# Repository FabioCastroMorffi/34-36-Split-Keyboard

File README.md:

# Raw Split
## Overview

Raw Split is a wired 36 key split keyboard made with 3 PCB layers and powered by an RP pico 2040 on each side. I'm using the Miryoku ZMK as the layout and  I decided to go for a smaller split keyboard for two main reasons: I want it to be portable, mainly so I can use it in class, and I wanted to be under (or very close to) the 50$ mark.

## Motivation
After finishing my design for Hackpad, which was an introduction to PCB Design and 3D modelling, I was confident I could go build a bigger project in a more efficient manner but I was completely wrong. I got sent to the Valley of Stupidity earlier than expected. 

I had an initial idea with a Split Keyboard that would have magnetic sides but I wasn't proud of the design I came up with (and it wasnt printable) so I decided to scrap it up and do it again with a different idea. The change was mainly on the fact that I abhorred 3D modelling of the top/side and bottom so on the Raw Split I decided to only use PCBs for the full design; the raw aesthetic of the build is where the name comes from -- I'm not very creative with names.

## PCBs

### Center

### Top

### Bottom

## CAD
[Direct link on Onshape](https://cad.onshape.com/documents/60adbd5316aad71d4d3bcb16/w/73c77201f5fbc04cf68d7350/e/32bb371216fb4a7634cbbee2?renderMode=0&uiState=686715ac173d9866c8e98733)

Thank you Onshape for being so easy to work with (shame on the horrible experience that is Fusion360's online services for students). I really need to emphasize how much better OnShape is on web, because the initial horrible experience I had with Fusion Online or trying to install a Linux version of Fusion was horrible and made me waste a lot of time. 

Here's the overview of the right split:

The total height of the keyboard will be 24.8 mm. The three PCBs measure 1.6 mm in height, the small standoff will have a height of 4 mm while the big one will have a size 6 mm. Finally the height from the top plate to the top of the keycap is approximally 10 mm. 

## BOM

| Quantity | Item                                 | Price (CAD) | Vendor         | Link                                                                 |
|----------|--------------------------------------|-------------|----------------|----------------------------------------------------------------------|
| 2        | RP Pico 2040 Green with Pin          | 6.42        | Aliexpress     | [Link](https://shorturl.at/I2swX)       |
| 1        | 40 PCS kailh box V2 (linear switches)| 1.38(with welcome deal)      | Aliexpress     | [Link](https://www.aliexpress.com/item/1005005704076690.html) |                                                  
| 1        | 100 PCS Through Hole Diodes (1N4148) | 2.80        | Aliexpress     | [Link](https://shorturl.at/UQSGh)     |
| 2        | 0.91 Inch 128x32 Oled Display        | 5.00        | Aliexpress     | [Link](https://www.aliexpress.com/item/32709141534.html)            |
| 2        | 20 pcs Blank DSA Keycaps             | 12.5        | Aliexpress     | [link](https://shorturl.at/4GHxS)                                   |
| 1        | 10 PCS PJ-320A Jack Receptacle       | 1.58        | Aliexpress     | [Link](https://www.aliexpress.com/item/1005004960903273.html)       |
| 1        | 20 pcs SW-Push 6x6x4.3mm             | 0.26        | Aliexpress     | [Link](https://shorturl.at/fNnse) |
| 1        | 50 pcs Brass Female to Female Standoffs M2x3mm | 2.72        | Aliexpress     | [Link](https://shorturl.at/DMM1S)|
| 1        | 50 pcs Nylon Female to Female Standoffs M2x6mm | 1.28        | Aliexpress     | [Link](https://shorturl.at/DEXHc)
| 2        | 50 pcs M2 5mm and M2 10 mm           | 4.5         | Aliexpress | [Link](https://shorturl.at/Y6ADS) |
| 1        | Antislip Circular Pads 2mm           | 2.97        | Aliexpress | [Link](https://shorturl.at/uavc9)
| 1        | PCB Manufacturing Center             | 13.04  (without coupon)     | JLCPCB         | 
| 1        | PCB Manufacturing Top                | 12.64  (without coupon)     | JLCPCB         |
| 1        | PCB Manufacturing Bottom             | 12.50  (without coupon)     | JLCPCB         |

|Total (CAD, after taxes and after 20$ JLcPCB Coupon)| Total (USD, after taxes and after 20$ JLcPCB Coupon)|
|---------------|--|
|69|50.69|

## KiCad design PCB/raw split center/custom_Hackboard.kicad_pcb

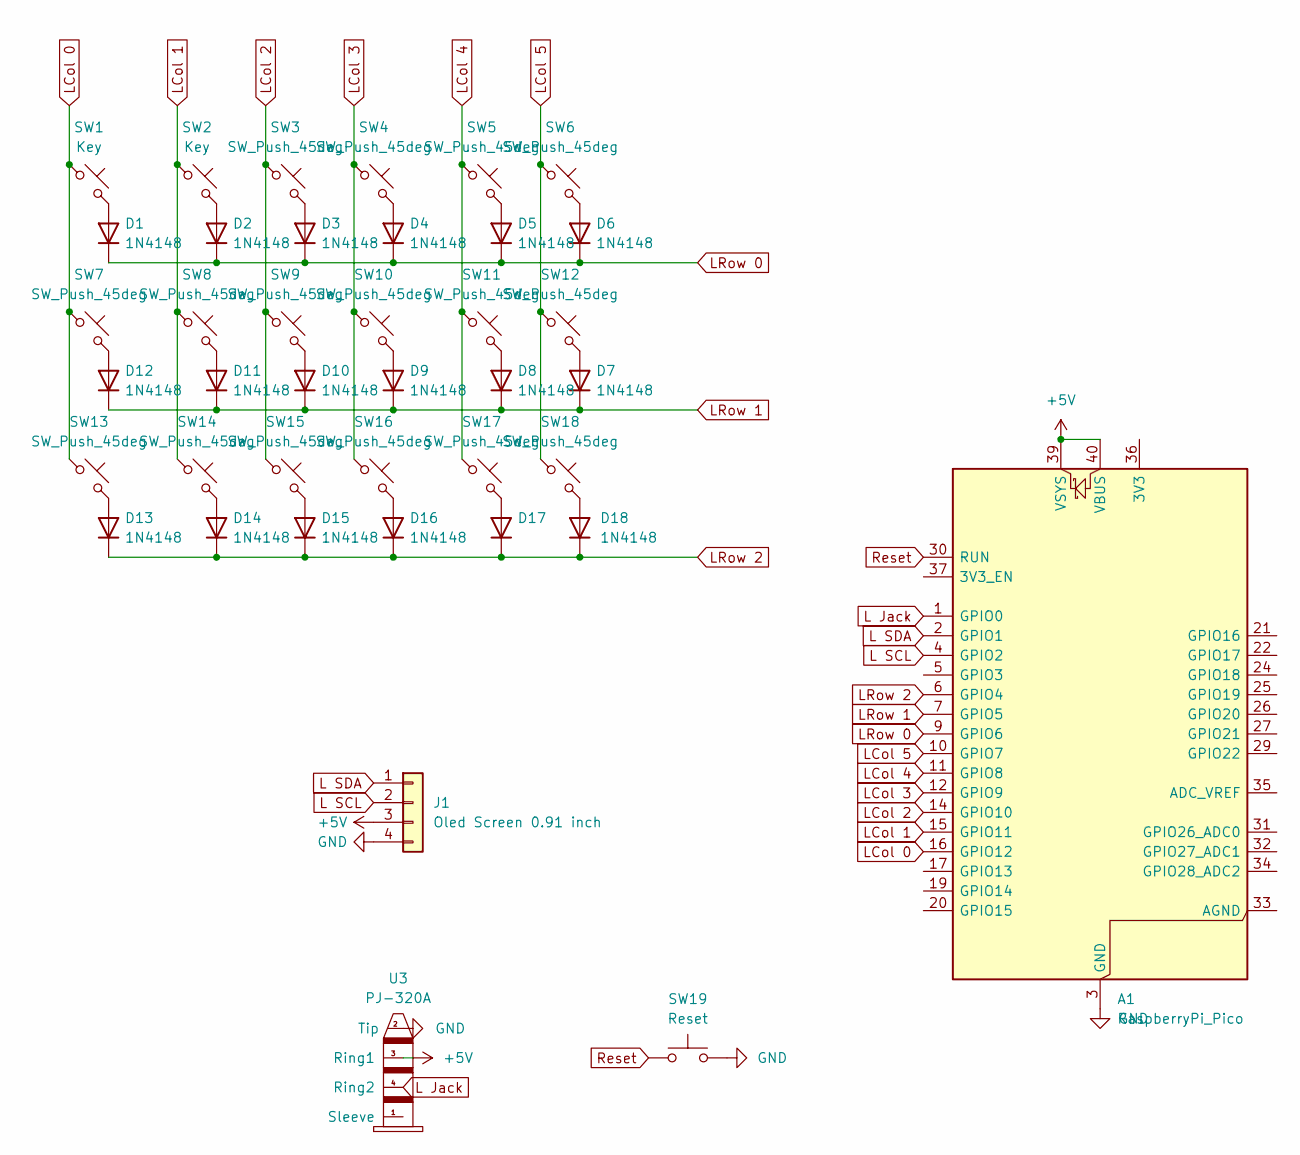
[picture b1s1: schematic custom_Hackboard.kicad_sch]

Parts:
A1: RaspberryPi_Pico; RaspberryPi_Pico_Common_Unspecified
D1, D2, D3, D4, D5, D6, D7, D8, D9, D10, D11, D12, D13, D14, D15, D16, D17, D18: 1N4148; D_DO-35_SOD27_P7.62mm_Horizontal
J1: Oled Screen 0.91 inch; SSD1306-0.91-OLED-4pin-128x32
SW1, SW2: Key; Cherry MX 1u
SW3, SW4, SW5, SW6, SW7, SW8, SW9, SW10, SW11, SW12, SW13, SW14, SW15, SW16, SW17, SW18: SW_Push_45deg; Cherry MX 1u
SW19: Reset; SW_PUSH_6mm_H5mm
U3: PJ-320A

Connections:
+5V: A1.39 (VSYS), A1.40 (VBUS), J1.3, U3.3 (Ring1)
GND: A1.3 (GND), A1.8 (GND), A1.13 (GND), A1.18 (GND), A1.23 (GND), A1.28 (GND), A1.38 (GND), J1.4, SW19.2, U3.2 (Tip); also elsewhere on the board
L Jack: A1.1 (GPIO0), U3.4 (Ring2)
L SCL: A1.4 (GPIO2), J1.2
L SDA: A1.2 (GPIO1), J1.1
LCol 0: A1.16 (GPIO12), SW1.1, SW7.1, SW13.1
LCol 1: A1.15 (GPIO11), SW2.1, SW8.1, SW14.1
LCol 2: A1.14 (GPIO10), SW3.1, SW9.1, SW15.1
LCol 3: A1.12 (GPIO9), SW4.1, SW10.1, SW16.1
LCol 4: A1.11 (GPIO8), SW5.1, SW11.1, SW17.1
LCol 5: A1.10 (GPIO7), SW6.1, SW12.1, SW18.1
LRow 0: A1.9 (GPIO6), D1.1 (K), D2.1 (K), D3.1 (K), D4.1 (K), D5.1 (K), D6.1 (K)
LRow 1: A1.7 (GPIO5), D7.1 (K), D8.1 (K), D9.1 (K), D10.1 (K), D11.1 (K), D12.1 (K)
LRow 2: A1.6 (GPIO4), D13.1 (K), D14.1 (K), D15.1 (K), D16.1 (K), D17.1 (K), D18.1 (K)
unnamed: D1.2 (A), SW1.2
unnamed: D2.2 (A), SW2.2
unnamed: D3.2 (A), SW3.2
unnamed: D4.2 (A), SW4.2
unnamed: D5.2 (A), SW5.2
unnamed: D6.2 (A), SW6.2
unnamed: D7.2 (A), SW12.2
unnamed: D8.2 (A), SW11.2
unnamed: D9.2 (A), SW10.2
unnamed: D10.2 (A), SW9.2
unnamed: D11.2 (A), SW8.2
unnamed: D12.2 (A), SW7.2
unnamed: D13.2 (A), SW13.2
unnamed: D14.2 (A), SW14.2
unnamed: D15.2 (A), SW15.2
unnamed: D16.2 (A), SW16.2
unnamed: D17.2 (A), SW17.2
unnamed: D18.2 (A), SW18.2
Reset: A1.30 (RUN), SW19.1; also elsewhere on the board

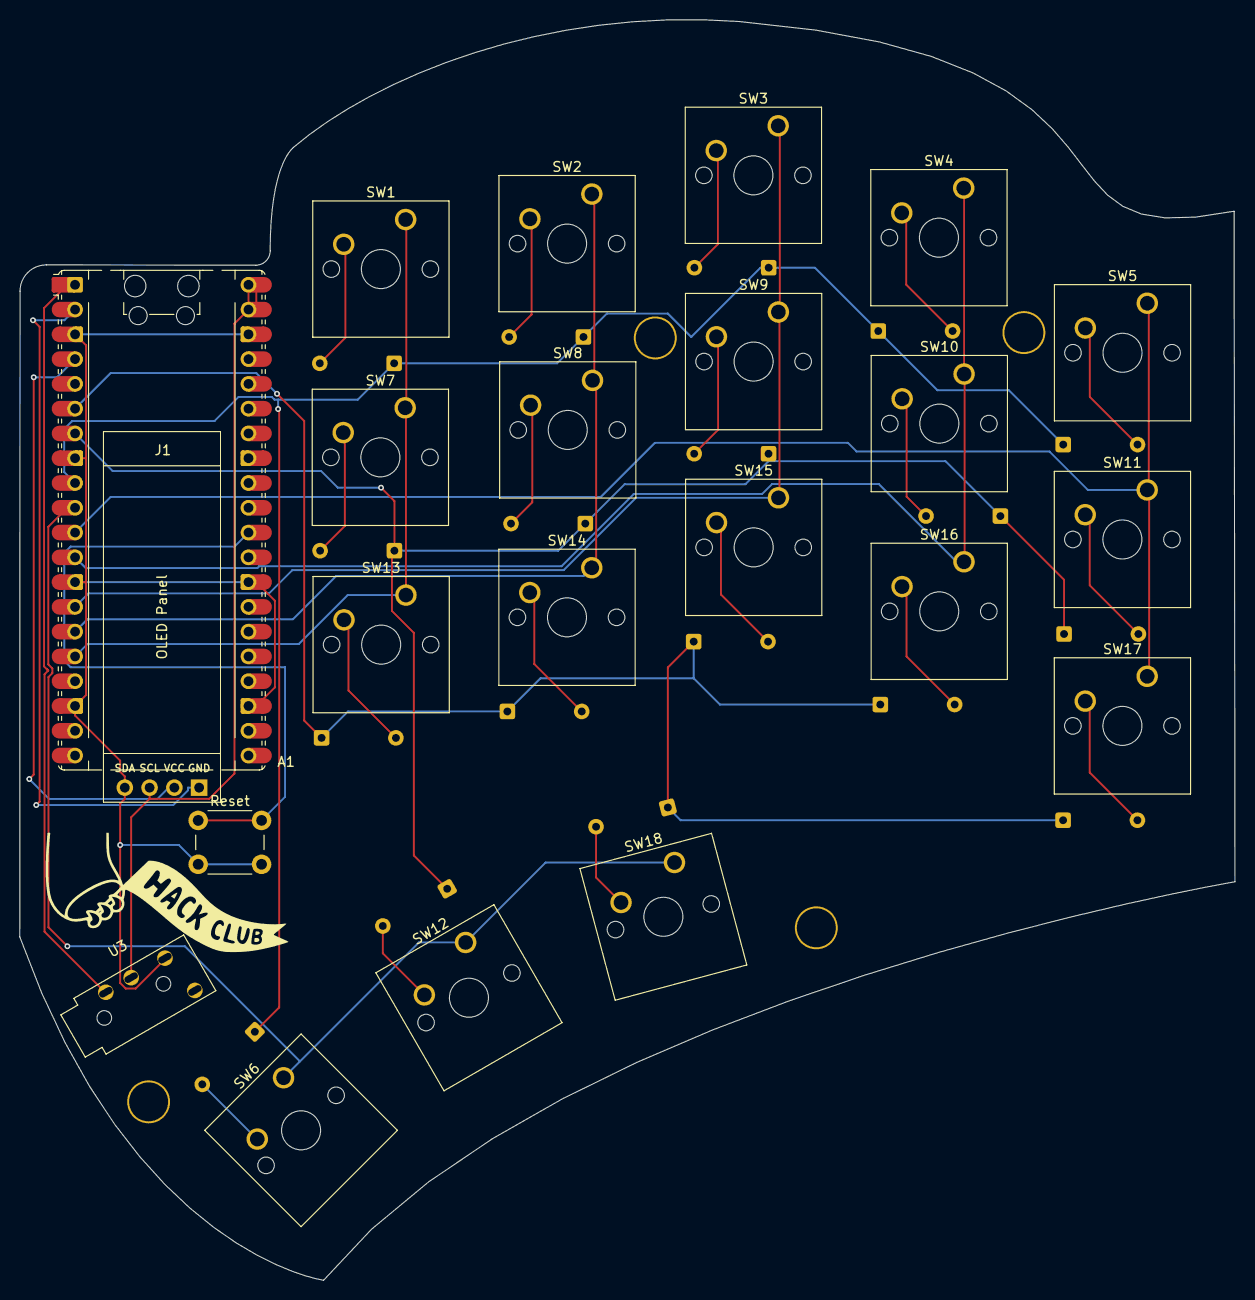
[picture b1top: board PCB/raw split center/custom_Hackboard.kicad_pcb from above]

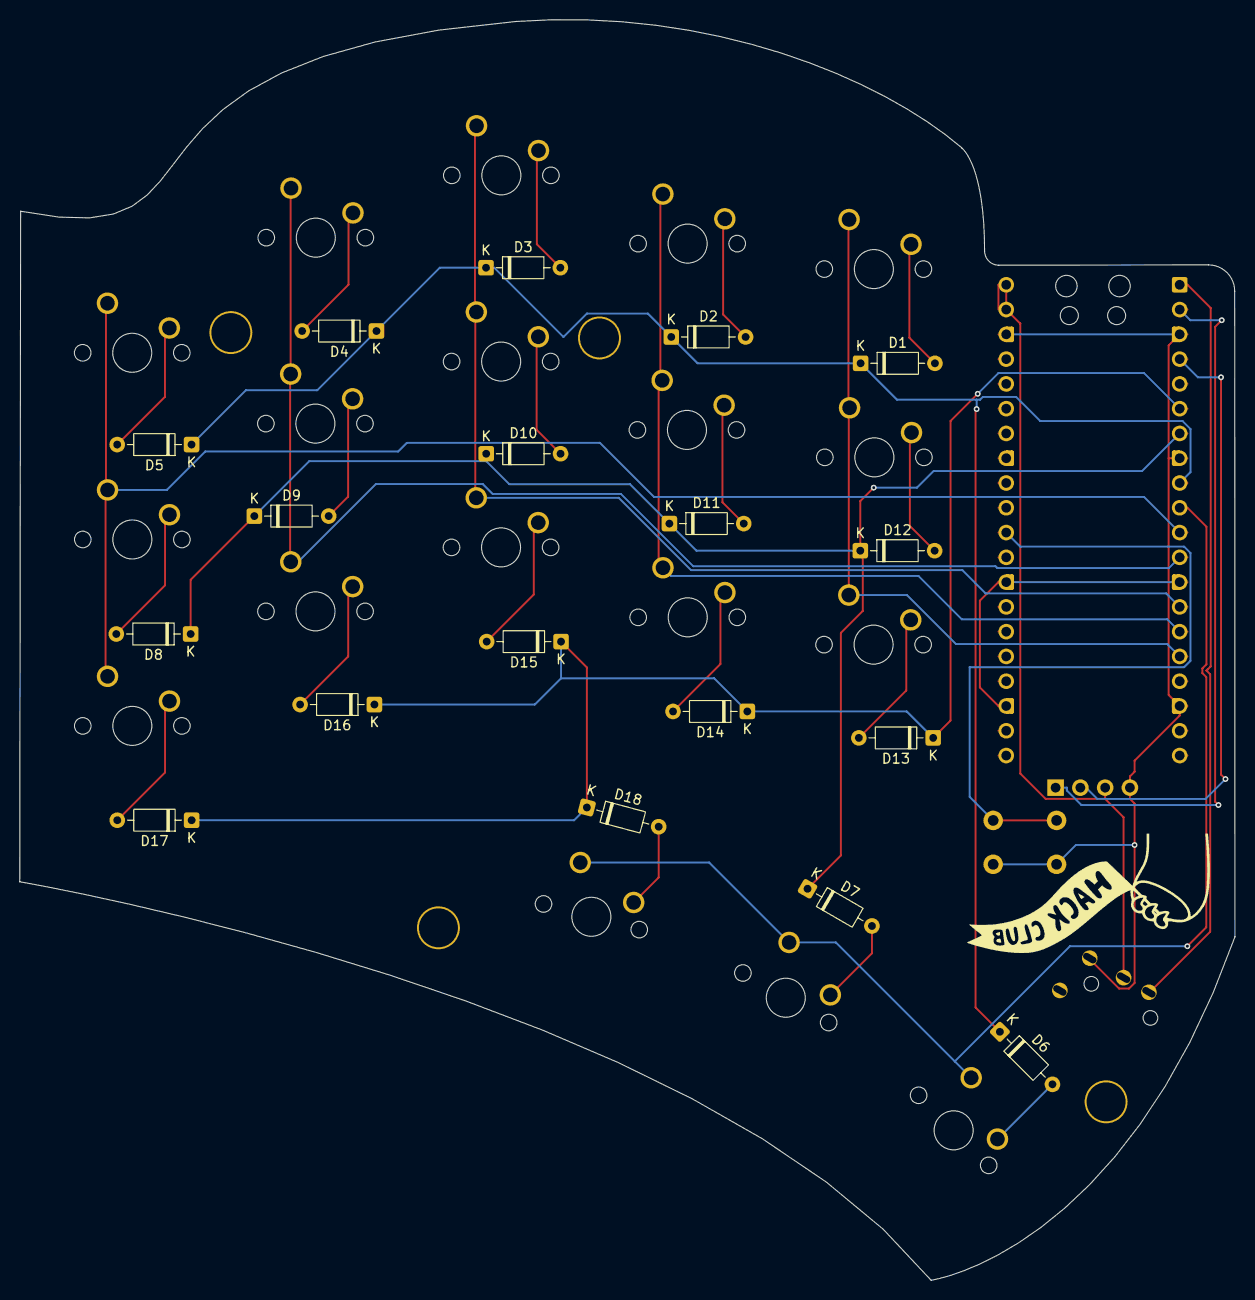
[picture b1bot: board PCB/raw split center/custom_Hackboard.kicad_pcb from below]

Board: 2 copper layers, 124.6 x 129.2 mm, 42 parts (19 on the bottom side), 33 nets.

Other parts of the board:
  : LOGO; hackclub
  #2: LOGO; hackclub
Reset: Reset; SW_PUSH_6mm_H5mm

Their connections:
GND: Reset.2; also elsewhere on the board
Reset: Reset.1; also elsewhere on the board

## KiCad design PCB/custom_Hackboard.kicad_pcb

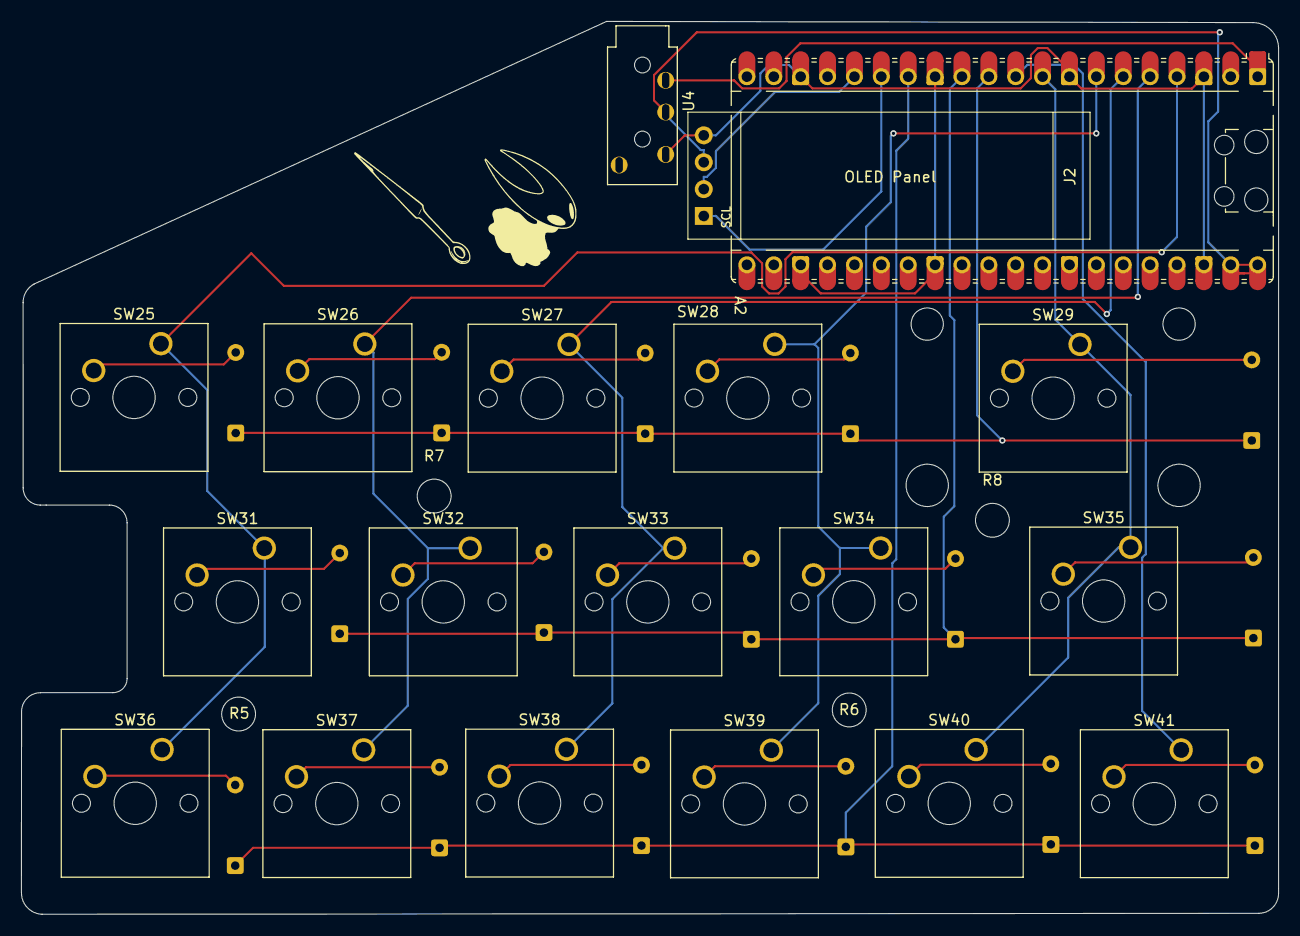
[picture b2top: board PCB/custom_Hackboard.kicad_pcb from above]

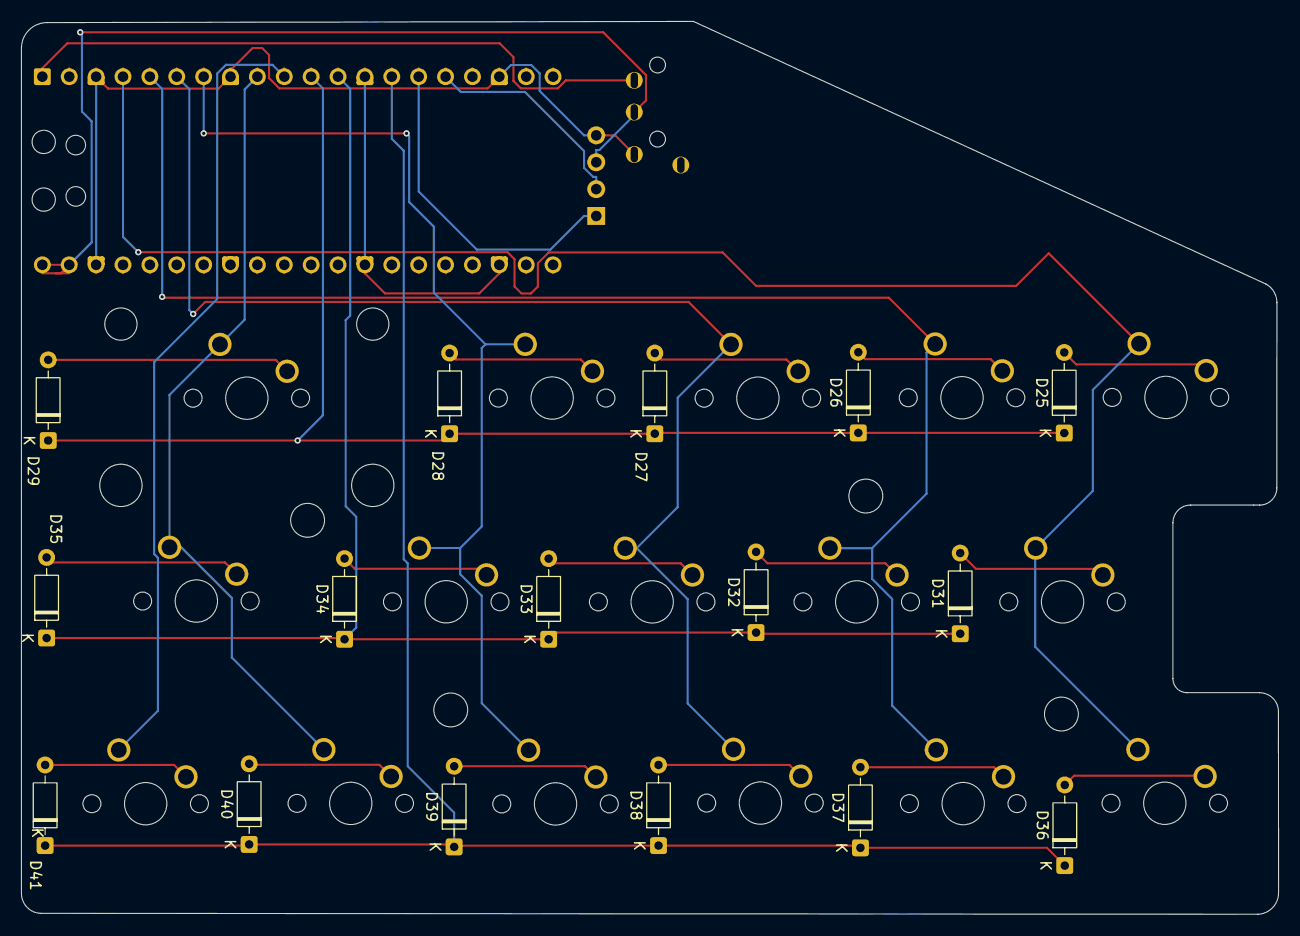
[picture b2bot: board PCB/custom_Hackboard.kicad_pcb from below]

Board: 2 copper layers, 118.8 x 84.4 mm, 40 parts (16 on the bottom side), 30 nets.

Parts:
  : LOGO; hornet_needle
A2: RaspberryPi_Pico; RaspberryPi_Pico_Common_Unspecified
D25, D26, D27, D28, D29, D31, D32, D33, D34, D35, D36, D37, D38, D39, D40, D41: 1N4148; D_DO-35_SOD27_P7.62mm_Horizontal
J2: Conn_01x04; SSD1306-0.91-OLED-4pin-128x32
R5, R6, R7, R8: MountingHole_3.2mm_M3_ISO7380
SW25, SW26, SW27, SW28, SW31, SW32, SW33, SW34, SW36, SW37, SW38, SW39, SW40, SW41: SW_Push_45deg; Cherry MX 1u
SW29: SW_Push_45deg; SW_Cherry_MX_2.00u_PCB
SW35: SW_Push_45deg; SW_Cherry_MX_1.50u_PCB
U4: PJ-320A

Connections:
/GND_R: A2.3 (GND), A2.8 (GND), A2.13 (GND), A2.18 (GND), A2.23 (GND), A2.28 (GND), A2.38 (GND), J2.4, U4.2 (Tip)
/PWR_R: A2.39 (VSYS), A2.40 (VBUS), J2.3, U4.3 (Ring1)
unnamed: D25.2 (A), SW25.2
unnamed: D26.2 (A), SW26.2
unnamed: D27.2 (A), SW27.2
unnamed: D28.2 (A), SW28.2
unnamed: D29.2 (A), SW29.2
unnamed: D31.2 (A), SW31.2
unnamed: D32.2 (A), SW32.2
unnamed: D33.2 (A), SW33.2
unnamed: D34.2 (A), SW34.2
unnamed: D35.2 (A), SW35.2
unnamed: D36.2 (A), SW36.2
unnamed: D37.2 (A), SW37.2
unnamed: D38.2 (A), SW38.2
unnamed: D39.2 (A), SW39.2
unnamed: D40.2 (A), SW40.2
unnamed: D41.2 (A), SW41.2
R Jack: A2.1 (GPIO0), U4.4 (Ring2)
R SCL: A2.16 (GPIO12), J2.2
R SDA: A2.15 (GPIO11), J2.1
RCol 0: A2.4 (GPIO2), SW25.1, SW31.1, SW36.1
RCol 1: A2.5 (GPIO3), SW26.1, SW32.1, SW37.1
RCol 2: A2.6 (GPIO4), SW27.1, SW33.1, SW38.1
RCol 3: A2.7 (GPIO5), SW28.1, SW34.1, SW39.1
RCol 4: A2.9 (GPIO6), SW29.1, SW35.1, SW40.1
RCol 5: A2.10 (GPIO7), SW41.1
RRow 0: A2.11 (GPIO8), D25.1 (K), D26.1 (K), D27.1 (K), D28.1 (K), D29.1 (K)
RRow 1: A2.12 (GPIO9), D31.1 (K), D32.1 (K), D33.1 (K), D34.1 (K), D35.1 (K)
RRow 2: A2.14 (GPIO10), D36.1 (K), D37.1 (K), D38.1 (K), D39.1 (K), D40.1 (K), D41.1 (K)

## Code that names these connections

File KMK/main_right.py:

import board
import displayio
import terminalio
import busio

from kb import KMKKeyboard
from kmk.scanners import DiodeOrientation
from kmk.keys import KC
from kmk.modules.layers import Layers
from kmk.modules.split import Split, SplitSide, SplitType

from adafruit_display_text import label
from adafruit_ssd1306 import SSD1306_I2C

keyboard = KMKKeyboard()

# Pins
keyboard.col_pins = (board.GPIO12, board.board.GPIO11, board.GPIO10, board.GPIO9, board.GPIO8, board.GPIO7)
keyboard.row_pins = (board.GPIO6, board.GPIO5, board.GPIO4)
keyboard.diode_orientation = DiodeOrientation.COL2ROW

#Oled for text display

displayio.release_displays()
i2c = busio.I2C(board.GPIO1, board.GPIO2)  # might reverse SDA and SCL if incorrect

display = SSD1306_I2C(38, 12, i2c)
splash = displayio.Group()

text_area = label.Label(terminalio.FONT, text="RAW SPLIT", x=2, y=10)
splash.append(text_area)
display.show(splash)


# Split Side
split_side = SplitSide.RIGHT


split = Split(split_type=SplitType.UART, split_side=split_side)

layers = Layers()

keyboard.modules = [layers, split]

# Key's reassignment

_______ = KC.TRNS



LOWER = KC.MO(2)
RAISE = KC.MO(1)


# fmt:off
keyboard.keymap = [
    [  #QWERTY
        KC.Q,    KC.W,    KC.E,    KC.R,    KC.T,                         KC.Y,    KC.U,    KC.I,    KC.O,   KC.P,
        KC.A,    KC.S,    KC.D,    KC.F,    KC.G,                         KC.H,    KC.J,    KC.K,    KC.L, KC.SCLN,
        KC.Z,    KC.X,    KC.C,    KC.V,    KC.B,                         KC.N,    KC.M, KC.COMM,  KC.DOT, KC.SLSH,
                                    KC.LCTL,   LOWER,  KC.SPC,     KC.BSPC,    RAISE,  KC.ENT,
    ],
    [  #RAISE
        KC.N1,   KC.N2,   KC.N3,   KC.N4,   KC.N5,                        KC.N6,   KC.N7,   KC.N8,   KC.N9,   KC.N0,
        KC.TAB,  KC.LEFT, KC.DOWN, KC.UP,   KC.RGHT,                      KC.NO, KC.MINS, KC.EQL,  KC.LBRC, KC.RBRC,
        KC.LCTL, KC.GRV,  KC.LGUI, KC.LALT, KC.NO,                      KC.NO, KC.NO, KC.NO, KC.BSLS, KC.QUOT,
                                    KC.NO, KC.NO, KC.NO,      KC.NO, KC.NO, KC.NO,
    ],
    [  #LOWER
        KC.EXLM, KC.AT,   KC.HASH, KC.DLR,  KC.PERC,      KC.CIRC, KC.AMPR, KC.ASTR, KC.LPRN, KC.RPRN,
        KC.ESC,  KC.NO, KC.NO, KC.NO, KC.NO,      KC.NO, KC.UNDS, KC.PLUS, KC.LCBR, KC.RCBR,
        KC.CAPS, KC.TILD, KC.NO, KC.NO, KC.NO,      KC.NO, KC.NO, KC.NO, KC.PIPE,  KC.DQT,
                            KC.NO, KC.NO, KC.NO,      KC.ENT,  KC.NO, KC.DEL
    ]
]
# fmt:on

if __name__ == '__main__':
    keyboard.go()

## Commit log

2025-06-05 journal
2025-06-07 adding assets
2025-06-07 updating assets
2025-06-11 more jpegs
2025-06-11 more
2025-06-12 addding pngs
2025-06-15 more pngs
2025-06-17 even more pngs
2025-06-17 whatev
2025-06-17 next
2025-06-18 what
2025-06-18 folder journal backups
2025-06-18 more stuff
2025-06-18 finished CAD design, missing finishing
2025-06-18 adding PCB, 3d model, KMK and finishing README
2025-06-18 adding
2025-07-05 added pcb files and removed som directories
2025-07-05 replaced bom csv
2025-07-05 kmk files for right and left
